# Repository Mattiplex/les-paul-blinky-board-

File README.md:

# telecaster-blinky-board-
it's a telecaster baby

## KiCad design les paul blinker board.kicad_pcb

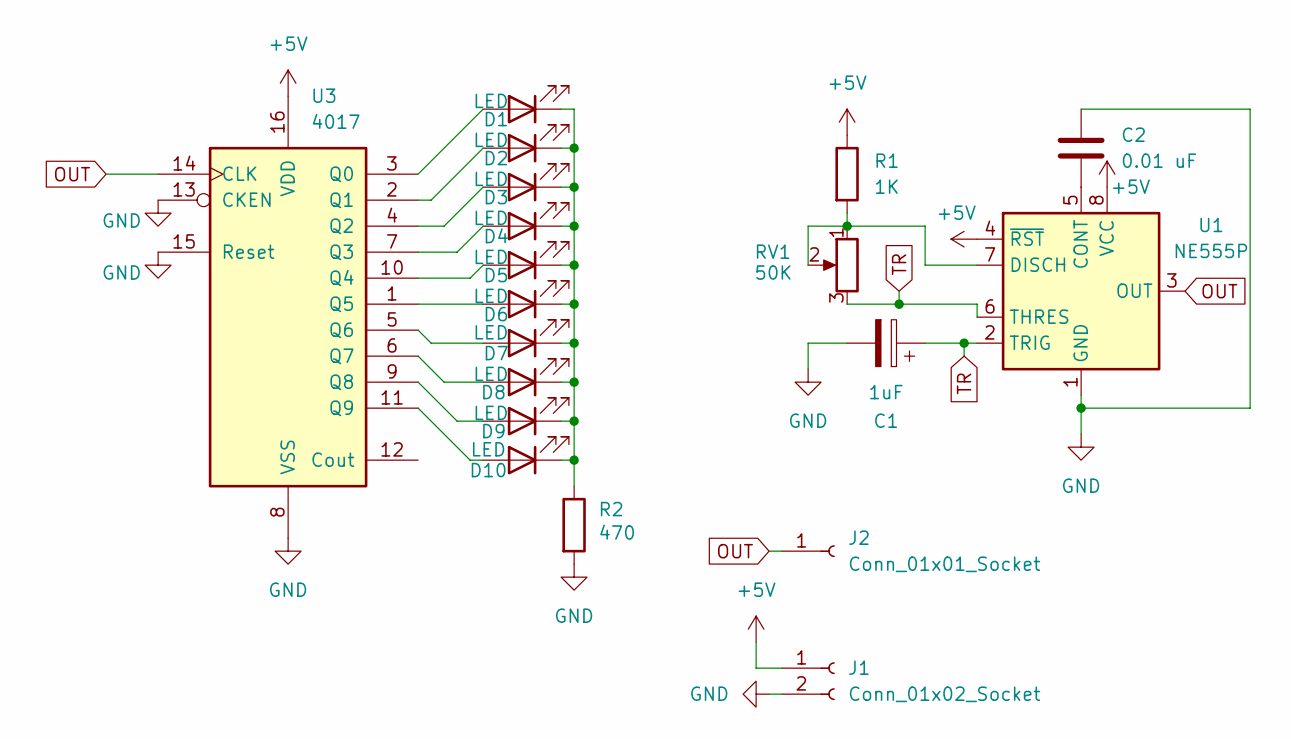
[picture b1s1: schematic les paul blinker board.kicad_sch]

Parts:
C1: 1uF; CP_Radial_D5.0mm_P2.00mm
C2: 0.01 uF; C_Disc_D7.0mm_W2.5mm_P5.00mm
D1, D2, D3, D4, D5, D6, D7, D8, D9, D10: LED; LED_D3.0mm
J1: Conn_01x02_Socket; PinSocket_1x02_P2.54mm_Vertical
J2: Conn_01x01_Socket; PinSocket_1x01_P2.54mm_Vertical
R1: 1K; R_Axial_DIN0207_L6.3mm_D2.5mm_P7.62mm_Horizontal
R2: 470; R_Axial_DIN0207_L6.3mm_D2.5mm_P7.62mm_Horizontal
RV1: 50K; Potentiometer_Vishay_T93YA_Vertical
U1: NE555P; DIP-8_W7.62mm
U3: 4017; DIP-16_W7.62mm

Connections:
+5V: J1.1, R1.1, U1.4 (~RST), U1.8 (VCC), U3.16 (VDD)
GND: C1.2, C2.1, J1.2, R2.2, U1.1 (GND), U3.8 (VSS), U3.13 (CKEN), U3.15 (Reset)
unnamed: D1.2 (A), U3.3 (Q0)
unnamed: D1.1 (K), D2.1 (K), D3.1 (K), D4.1 (K), D5.1 (K), D6.1 (K), D7.1 (K), D8.1 (K), D9.1 (K), D10.1 (K), R2.1
unnamed: D2.2 (A), U3.2 (Q1)
unnamed: D3.2 (A), U3.4 (Q2)
unnamed: D4.2 (A), U3.7 (Q3)
unnamed: D5.2 (A), U3.10 (Q4)
unnamed: D6.2 (A), U3.1 (Q5)
unnamed: D7.2 (A), U3.5 (Q6)
unnamed: D8.2 (A), U3.6 (Q7)
unnamed: D9.2 (A), U3.9 (Q8)
unnamed: D10.2 (A), U3.11 (Q9)
unnamed: C2.2, U1.5 (CONT)
unnamed: R1.2, RV1.1, RV1.2, U1.7 (DISCH)
OUT: J2.1 (Pin_1_1), U1.3 (OUT), U3.14 (CLK)
TR: C1.1, RV1.3, U1.2 (TRIG), U1.6 (THRES)

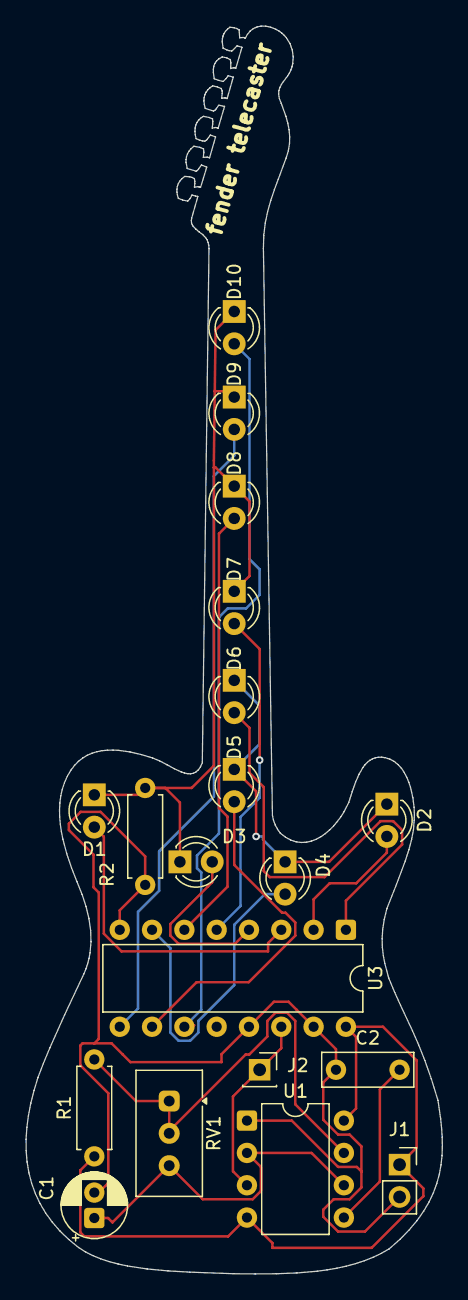
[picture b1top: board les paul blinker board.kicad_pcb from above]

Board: 2 copper layers, 32.7 x 98.1 mm, 19 parts (0 on the bottom side), 17 nets.
